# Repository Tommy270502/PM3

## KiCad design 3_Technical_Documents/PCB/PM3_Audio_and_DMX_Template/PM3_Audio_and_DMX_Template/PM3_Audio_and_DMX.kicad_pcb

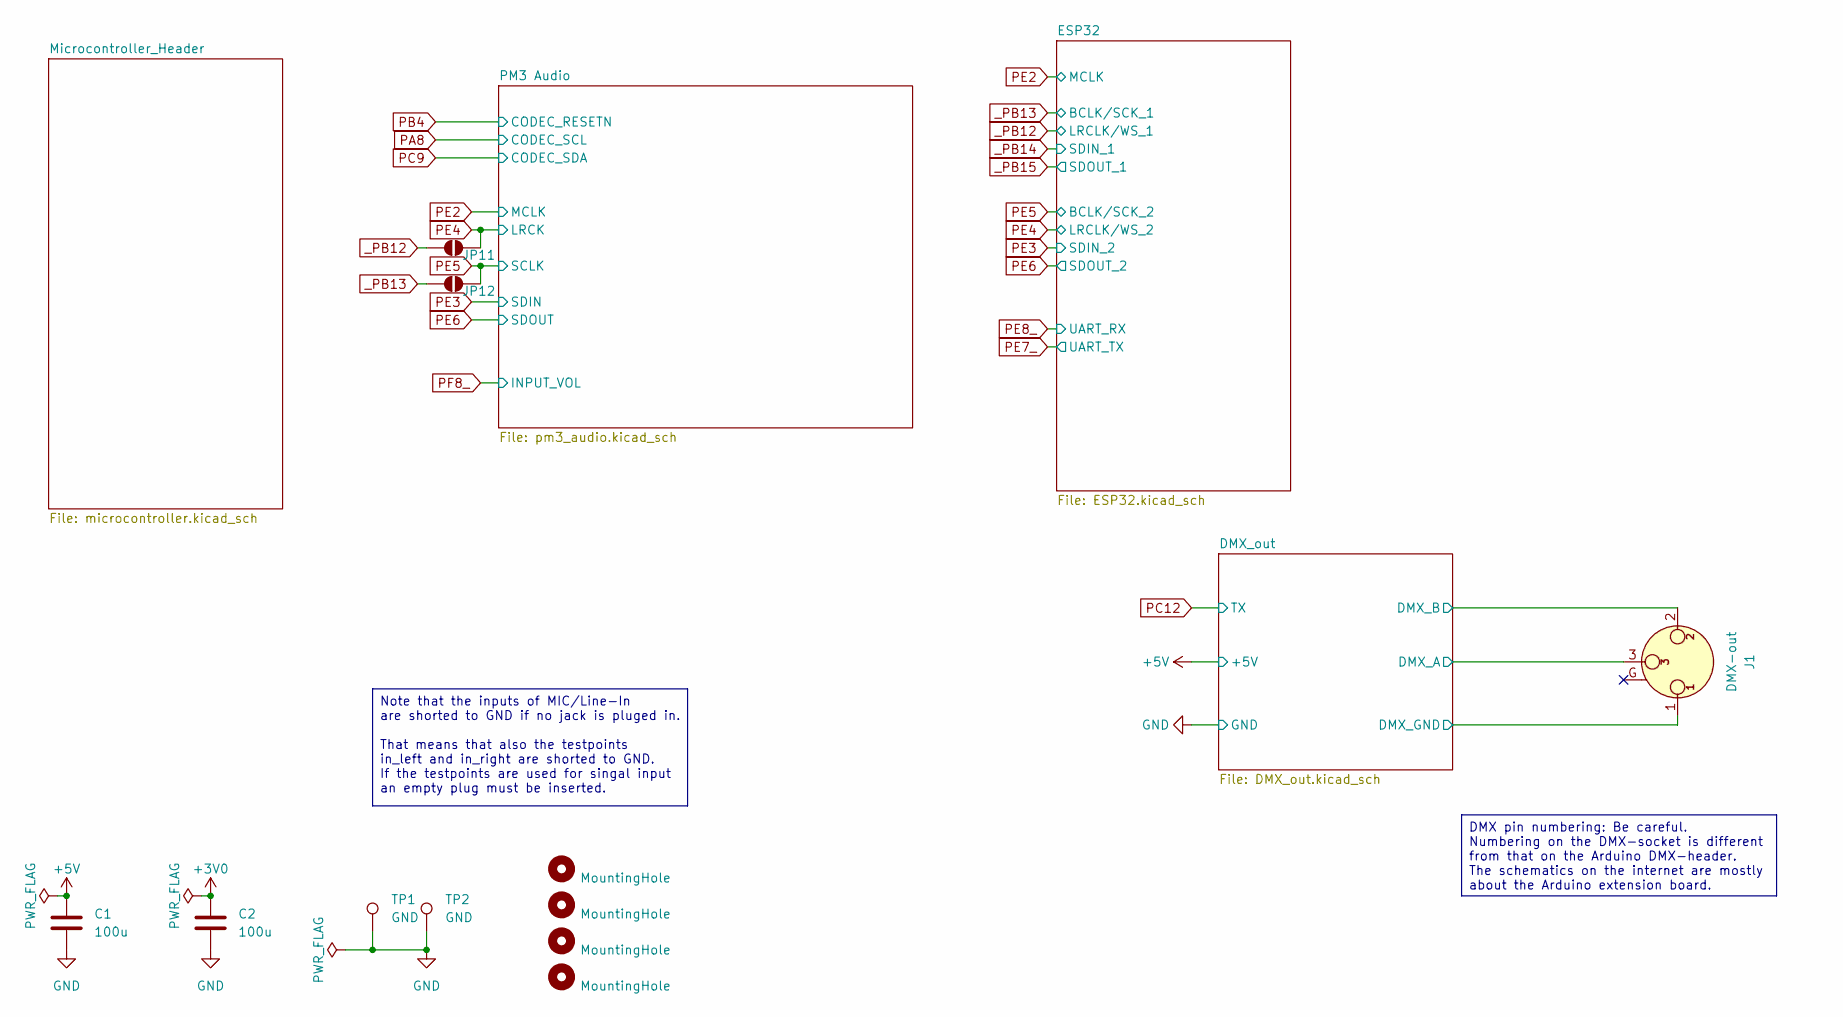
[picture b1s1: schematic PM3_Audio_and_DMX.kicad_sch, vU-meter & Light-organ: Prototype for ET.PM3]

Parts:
C1, C2: 100u; C_1206_3216Metric_Pad1.33x1.80mm_HandSolder; MPN C3216X5R1A107M160AC
H1, H2, H3, H4: MountingHole; MountingHole_3.2mm_M3_Pad_TopBottom
J1: DMX-out; Jack_XLR_Neutrik_NC3FAAH2_Horizontal
JP11, JP12: SolderJumper_2_Open; SolderJumper-2_P1.3mm_Open_RoundedPad1.0x1.5mm
TP1, TP2: GND; TestPoint_Loop_D2.60mm_Drill1.6mm_Beaded

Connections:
+5V: C1.1; also elsewhere on the board
/DMX_out/DMX_A: J1.3; also elsewhere on the board
/DMX_out/DMX_B: J1.2; also elsewhere on the board
DMX_GND: J1.1; also elsewhere on the board
GND: C1.2, C2.2, TP1.1, TP2.1; also elsewhere on the board
PE4: JP11.2 (B); also elsewhere on the board
PE5: JP12.2 (B); also elsewhere on the board
VL: C2.1; also elsewhere on the board
_PB12: JP11.1 (A); also elsewhere on the board
_PB13: JP12.1 (A); also elsewhere on the board

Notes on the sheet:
Note that the inputs of MIC/Line-In are shorted to GND if no jack is pluged in. That means that also the testpoints in_left and in_right are shorted to GND. If the testpoints are used for singal input an empty plug must be inserted.
DMX pin numbering: Be careful. Numbering on the DMX-socket is different from that on the Arduino DMX-header. The schematics on the internet are mostly about the Arduino extension board.

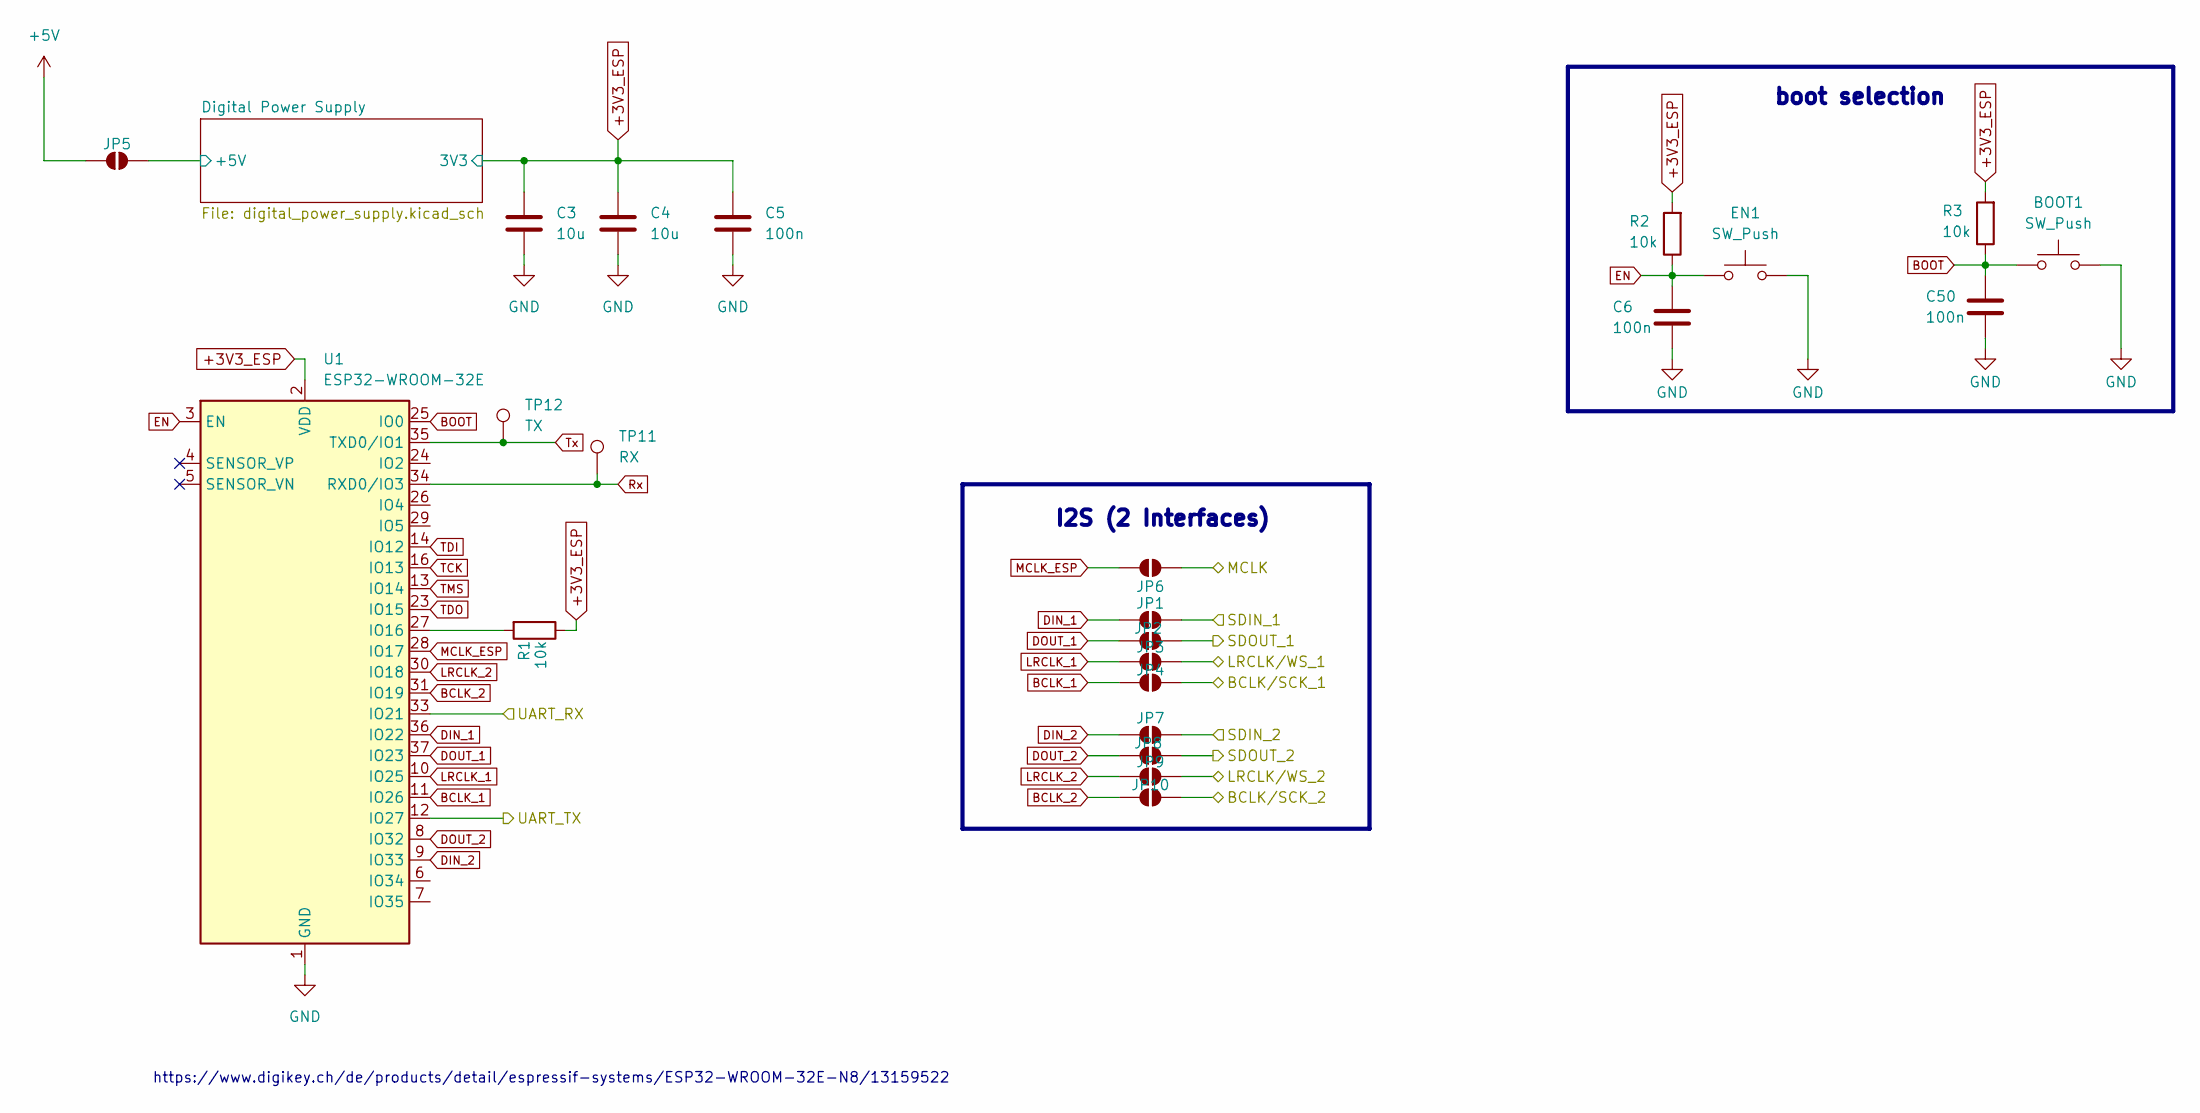
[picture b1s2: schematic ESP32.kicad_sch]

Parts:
BOOT1: SW_Push; SW_SPST_TL3342
C3, C4: 10u; C_1210_3225Metric; MPN GJ832ER7YA106KA12L
C5, C6, C50: 100n; C_0603_1608Metric; MPN GPC0603104-X7R
EN1: SW_Push; SW_SPST_TL3342
JP1, JP2, JP3, JP4, JP5, JP6, JP7, JP8, JP9, JP10: SolderJumper_2_Open; SolderJumper-2_P1.3mm_Open_RoundedPad1.0x1.5mm
R1, R2, R3: 10k; R_0603_1608Metric; MPN GPR060310K
TP11: RX
TP12: TX
U1: ESP32-WROOM-32E; ESP32-WROOM-32D

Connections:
+3V3_ESP: C3.1, C4.1, C5.1, R1.1, R2.2, R3.2, U1.2 (VDD); also elsewhere on the board
+5V: JP5.1 (A); also elsewhere on the board
/ESP32/Digital Power Supply/+5V: JP5.2 (B); also elsewhere on the board
BCLK_1: JP4.1 (A), U1.11 (IO26)
BCLK_2: JP10.1 (A), U1.31 (IO19)
BOOT: BOOT1.2, C50.1, R3.1, U1.25 (IO0)
DIN_1: JP1.1 (A), U1.36 (IO22)
DIN_2: JP7.1 (A), U1.9 (IO33)
DOUT_1: JP2.1 (A), U1.37 (IO23)
DOUT_2: JP8.1 (A), U1.8 (IO32)
EN: C6.1, EN1.2, R2.1, U1.3 (EN)
GND: BOOT1.1, C3.2, C4.2, C5.2, C6.2, C50.2, EN1.1, U1.1 (GND), U1.15 (GND), U1.38 (GND), U1.39 (GND); also elsewhere on the board
LRCLK_1: JP3.1 (A), U1.10 (IO25)
LRCLK_2: JP9.1 (A), U1.30 (IO18)
MCLK_ESP: JP6.1 (A), U1.28 (IO17)
unnamed: R1.2, U1.27 (IO16)
PE2: JP6.2 (B); also elsewhere on the board
PE3: JP7.2 (B); also elsewhere on the board
PE4: JP9.2 (B); also elsewhere on the board
PE5: JP10.2 (B); also elsewhere on the board
PE6: JP8.2 (B); also elsewhere on the board
PE7_: U1.12 (IO27); also elsewhere on the board
PE8_: U1.33 (IO21); also elsewhere on the board
Rx: TP11.1, U1.34 (RXD0/IO3)
TCK: U1.16 (IO13)
TDI: U1.14 (IO12)
TDO: U1.23 (IO15)
TMS: U1.13 (IO14)
Tx: TP12.1, U1.35 (TXD0/IO1)
_PB12: JP3.2 (B); also elsewhere on the board
_PB13: JP4.2 (B); also elsewhere on the board
_PB14: JP1.2 (B); also elsewhere on the board
_PB15: JP2.2 (B); also elsewhere on the board

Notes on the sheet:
boot selection
https://www.digikey.ch/de/products/detail/espressif-systems/ESP32-WROOM-32E-N8/13159522
I2S (2 Interfaces)

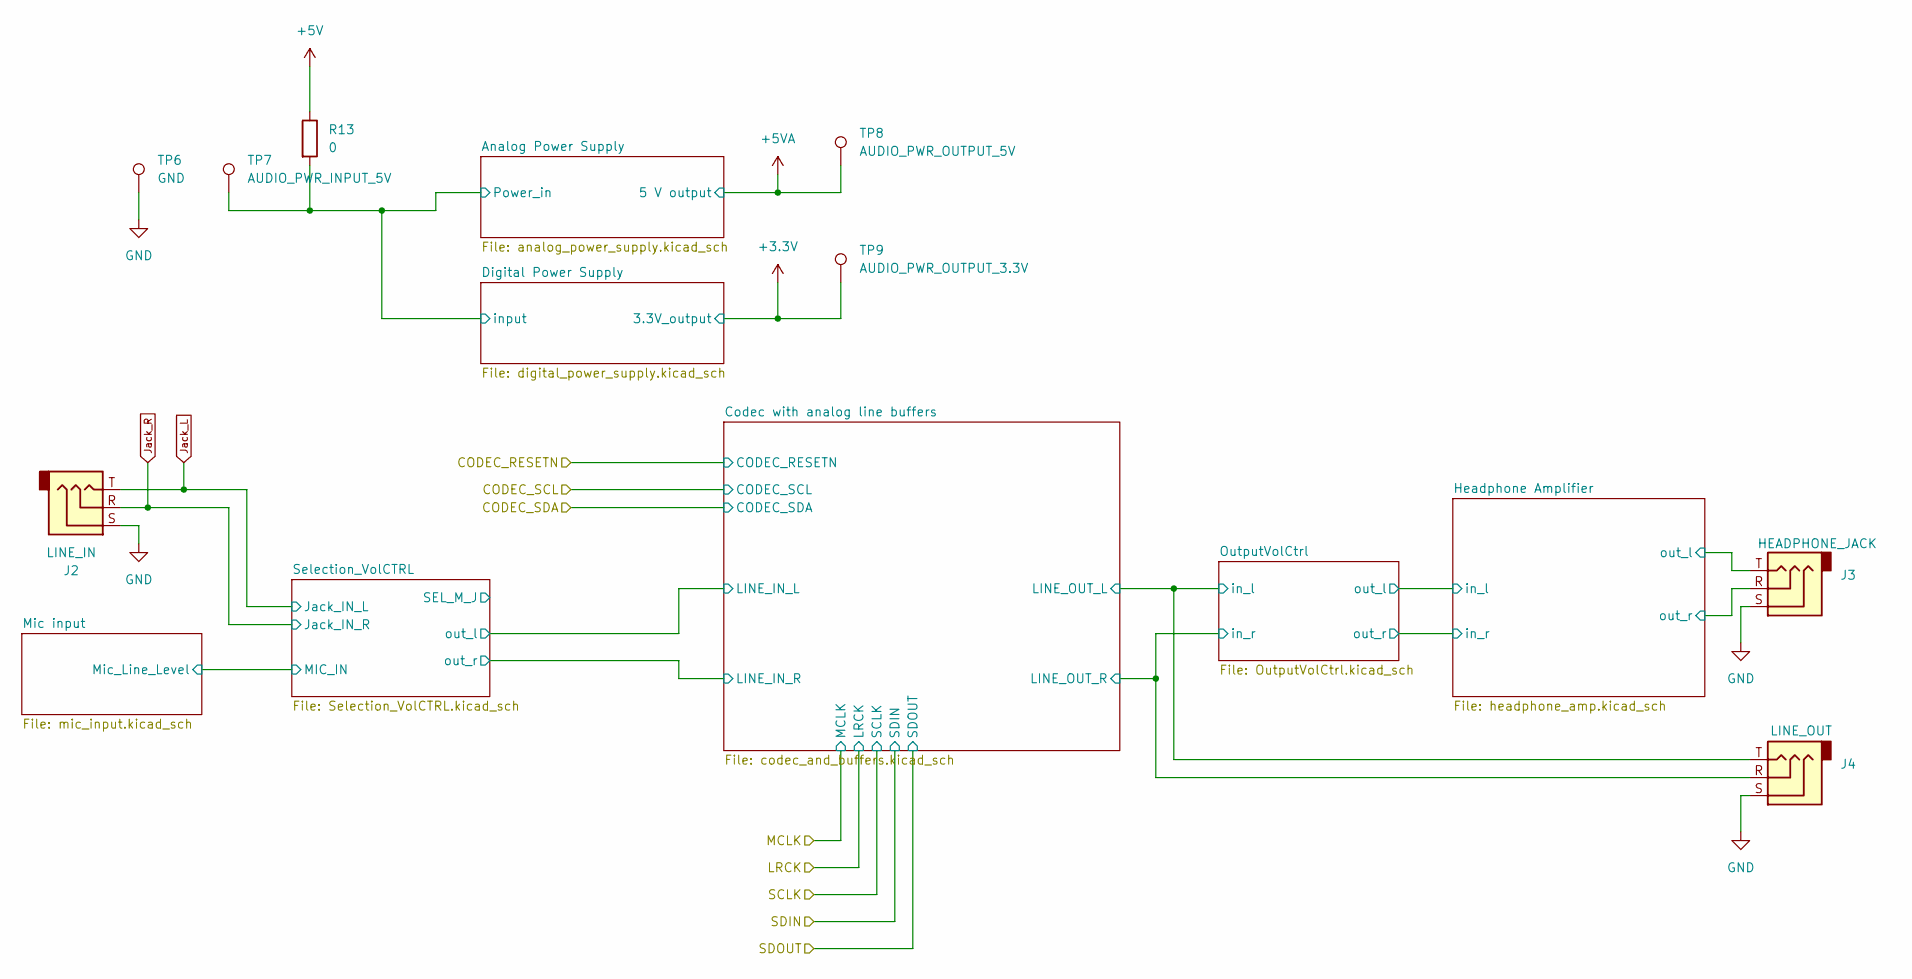
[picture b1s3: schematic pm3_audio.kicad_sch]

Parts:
J2: LINE_IN; Jack_3.5mm_CUI_SJ-3523-SMT_Horizontal; MPN SJ-3523-SMT-TR
J3: HEADPHONE_JACK; Jack_3.5mm_CUI_SJ-3523-SMT_Horizontal; MPN SJ-3523-SMT-TR
J4: LINE_OUT; Jack_3.5mm_CUI_SJ-3523-SMT_Horizontal; MPN SJ-3523-SMT-TR
R13: 0; R_0603_1608Metric; MPN GPR06030R
TP6: GND; TestPoint_Loop_D2.60mm_Drill1.6mm_Beaded
TP7: AUDIO_PWR_INPUT_5V; TestPoint_Loop_D2.60mm_Drill1.6mm_Beaded
TP8: AUDIO_PWR_OUTPUT_5V; TestPoint_Loop_D2.60mm_Drill1.6mm_Beaded
TP9: AUDIO_PWR_OUTPUT_3.3V; TestPoint_Loop_D2.60mm_Drill1.6mm_Beaded

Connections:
+5V: R13.1; also elsewhere on the board
/PM3 Audio/Analog Power Supply/Power_in: R13.2, TP7.1; also elsewhere on the board
/PM3 Audio/Codec with analog line buffers/LINE_OUT_L: J4.T; also elsewhere on the board
/PM3 Audio/Codec with analog line buffers/LINE_OUT_R: J4.R; also elsewhere on the board
/PM3 Audio/Headphone Amplifier/out_l: J3.T; also elsewhere on the board
/PM3 Audio/Headphone Amplifier/out_r: J3.R; also elsewhere on the board
GND: J2.S, J3.S, J4.S, TP6.1; also elsewhere on the board
Jack_L: J2.T; also elsewhere on the board
Jack_R: J2.R; also elsewhere on the board
VA: TP8.1; also elsewhere on the board
VD: TP9.1; also elsewhere on the board

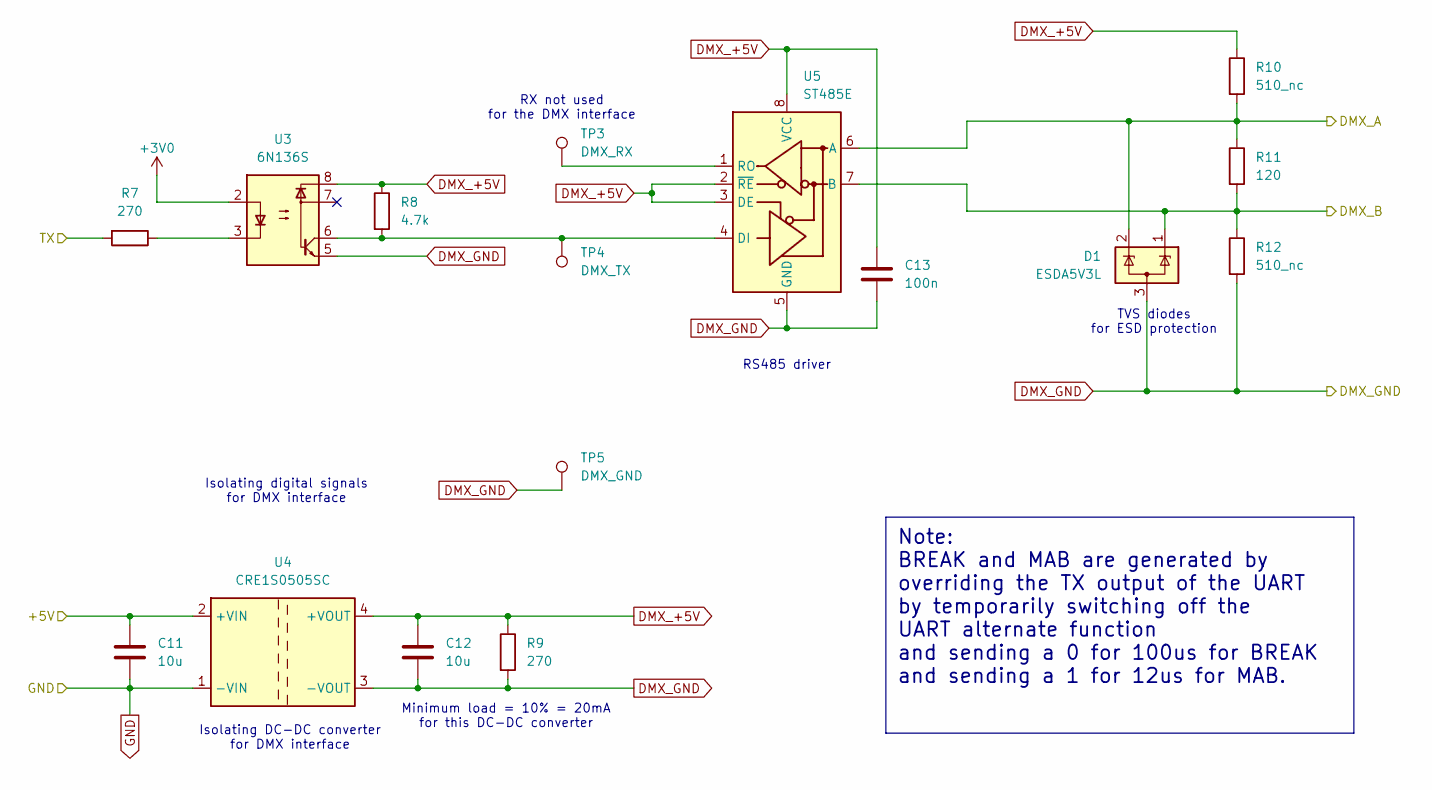
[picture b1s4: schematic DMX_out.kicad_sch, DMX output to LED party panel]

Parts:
C11, C12: 10u; C_0805_2012Metric_Pad1.18x1.45mm_HandSolder; MPN GPC0805106-35
C13: 100n; C_0805_2012Metric_Pad1.18x1.45mm_HandSolder; MPN GPC0805104
D1: ESDA5V3L; SOT-23-3; MPN ESDA5V3L
R7: 270; R_0603_1608Metric; MPN GPR0603270R
R8: 4.7k; R_0603_1608Metric; MPN GPR06034K7
R9: 270; R_0805_2012Metric; MPN GPR0805270R
R10, R12: 510_nc; R_0603_1608Metric
R11: 120; R_1206_3216Metric; MPN GPR1206120R
TP3: DMX_RX; TestPoint_Loop_D2.60mm_Drill1.6mm_Beaded
TP4: DMX_TX; TestPoint_Loop_D2.60mm_Drill1.6mm_Beaded
TP5: DMX_GND; TestPoint_Loop_D2.60mm_Drill1.6mm_Beaded
U3: 6N136S; SMDIP-8_W9.53mm; MPN 6N136S
U4: CRE1S0505SC; Converter_DCDC_Murata_CRE1xxxxxxSC_THT; MPN CRE1S0505SC
U5: ST485E; SOIC-8_3.9x4.9mm_P1.27mm; MPN ST485EBDR

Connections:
+5V: C11.1, U4.2 (+VIN); also elsewhere on the board
/DMX_out/DMX_A: D1.2 (K), R10.2, R11.1, U5.6 (A); also elsewhere on the board
/DMX_out/DMX_B: D1.1 (K), R11.2, R12.1, U5.7 (B); also elsewhere on the board
DMX_+5V: C12.1, C13.1, R8.1, R9.1, R10.1, U3.8, U4.4 (+VOUT), U5.2 (~RE), U5.3 (DE), U5.8 (VCC)
DMX_GND: C12.2, C13.2, D1.3 (A), R9.2, R12.2, TP5.1, U3.5, U4.3 (-VOUT), U5.5 (GND); also elsewhere on the board
GND: C11.2, U4.1 (-VIN); also elsewhere on the board
unnamed: R7.1, U3.3
unnamed: R8.2, TP4.1, U3.6, U5.4 (DI)
unnamed: TP3.1, U5.1 (RO)
PC12: R7.2; also elsewhere on the board
VL: U3.2; also elsewhere on the board

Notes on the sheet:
TVS diodes for ESD protection
Isolating digital signals for DMX interface
RX not used for the DMX interface
Minimum load = 10% = 20mA for this DC-DC converter
Isolating DC-DC converter for DMX interface
RS485 driver
Note: BREAK and MAB are generated by overriding the TX output of the UART by temporarily switching off the UART alternate function and sending a 0 for 100us for BREAK and sending a 1 for 12us for MAB.

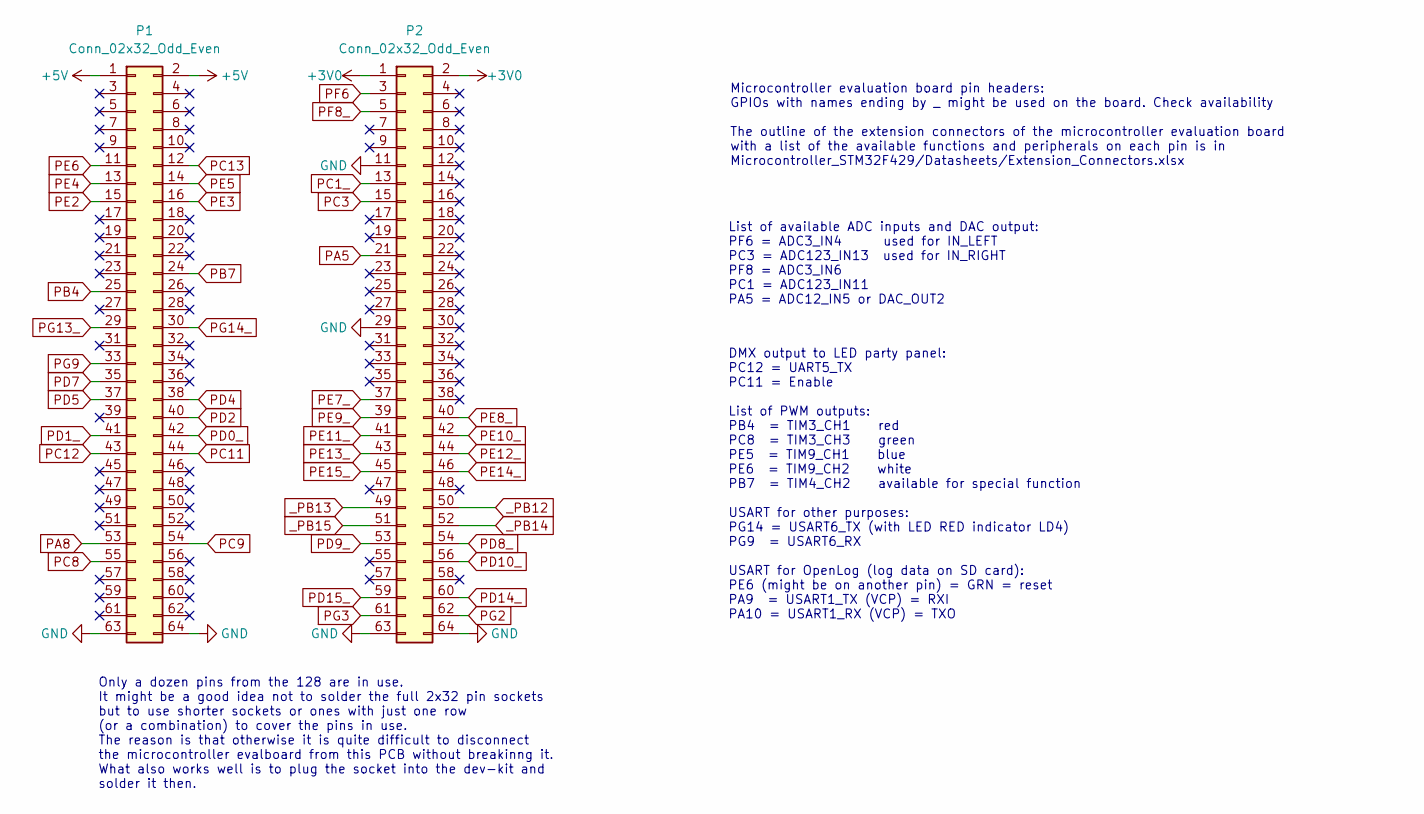
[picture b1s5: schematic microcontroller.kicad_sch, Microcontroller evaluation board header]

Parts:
P1, P2: Conn_02x32_Odd_Even; PinSocket_2x32_P2.54mm_Vertical

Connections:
+5V: P1.1, P1.2; also elsewhere on the board
GND: P1.63, P1.64, P2.11, P2.29, P2.63, P2.64; also elsewhere on the board
PA5: P2.21
PA8: P1.53; also elsewhere on the board
PB4: P1.25; also elsewhere on the board
PB7: P1.24
PC1_: P2.13
PC3: P2.15
PC8: P1.55
PC9: P1.54; also elsewhere on the board
PC11: P1.44
PC12: P1.43; also elsewhere on the board
PC13: P1.12
PD0_: P1.42
PD1_: P1.41
PD2: P1.40
PD4: P1.38
PD5: P1.37
PD7: P1.35
PD8_: P2.54
PD9_: P2.53
PD10_: P2.56
PD14_: P2.60
PD15_: P2.59
PE2: P1.15; also elsewhere on the board
PE3: P1.16; also elsewhere on the board
PE4: P1.13; also elsewhere on the board
PE5: P1.14; also elsewhere on the board
PE6: P1.11; also elsewhere on the board
PE7_: P2.37; also elsewhere on the board
PE8_: P2.40; also elsewhere on the board
PE9_: P2.39
PE10_: P2.42
PE11_: P2.41
PE12_: P2.44
PE13_: P2.43
PE14_: P2.46
PE15_: P2.45
PF6: P2.3
PF8_: P2.5
PG2: P2.62
PG3: P2.61
PG9: P1.33
PG13_: P1.29
PG14_: P1.30
VL: P2.1, P2.2; also elsewhere on the board
_PB12: P2.50; also elsewhere on the board
_PB13: P2.49; also elsewhere on the board
_PB14: P2.52; also elsewhere on the board
_PB15: P2.51; also elsewhere on the board

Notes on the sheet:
Only a dozen pins from the 128 are in use. It might be a good idea not to solder the full 2x32 pin sockets but to use shorter sockets or ones with just one row (or a combination) to cover the pins in use. The reason is that otherwise it is quite difficult to disconnect the microcontroller evalboard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
DMX output to LED party panel: PC12 = UART5_TX PC11 = Enable List of PWM outputs: PB4 = TIM3_CH1 red PC8 = TIM3_CH3 green PE5 = TIM9_CH1 blue PE6 = TIM9_CH2 white PB7 = TIM4_CH2 available for special function USART for other purposes: PG14 = USART6_TX (with LED RED indicator LD4) PG9 = USART6_RX US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
Microcontroller evaluation board pin headers: GPIOs with names ending by _ might be used on the board. Check availability The outline of the extension connectors of the microcontroller evaluation board with a list of the available functions and peripherals on each pin is in Microcontroller_STM32F42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
List of available ADC inputs and DAC output: PF6 = ADC3_IN4 used for IN_LEFT PC3 = ADC123_IN13 used for IN_RIGHT PF8 = ADC3_IN6 PC1 = ADC123_IN11 PA5 = ADC12_IN5 or DAC_OUT2

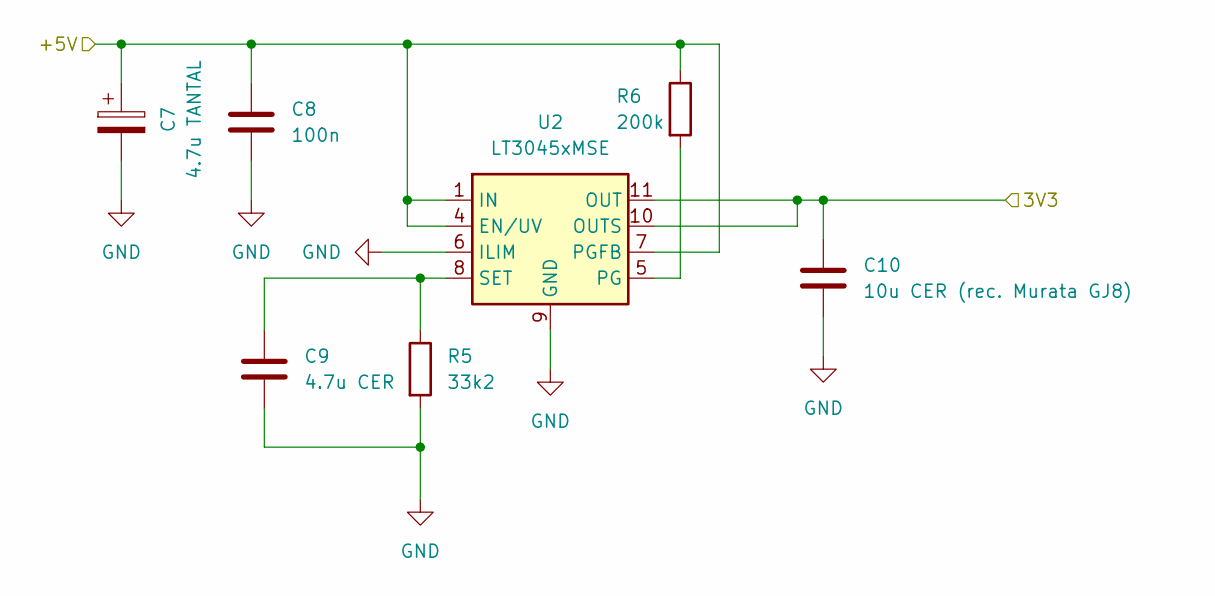
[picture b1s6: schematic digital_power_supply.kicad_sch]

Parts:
C7: 4.7u TANTAL; CP_EIA-3216-18_Kemet-A; MPN T495A475K010ATE1K3
C8: 100n; C_0603_1608Metric; MPN GPC0603104-X7R
C9: 4.7u CER; C_1210_3225Metric; MPN GPC1210475
C10: 10u CER (rec. Murata GJ8); C_1210_3225Metric; MPN GJ832ER7YA106KA12L
R5: 33k2; R_0603_1608Metric; MPN RC0603FR-0749K9L
R6: 200k; R_0603_1608Metric; MPN GPR0603200K
U2: LT3045xMSE; MSOP-12-1EP_3x4.039mm_P0.65mm_EP1.651x2.845mm; MPN LT3045EMSE

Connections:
+3V3_ESP: C10.1, U2.10 (OUTS), U2.11 (OUT), U2.12 (OUT); also elsewhere on the board
/ESP32/Digital Power Supply/+5V: C7.1, C8.1, R6.1, U2.1 (IN), U2.2 (IN), U2.3 (IN), U2.4 (EN/UV), U2.7 (PGFB); also elsewhere on the board
GND: C7.2, C8.2, C9.2, C10.2, R5.2, U2.6 (ILIM), U2.9 (GND), U2.13 (GND); also elsewhere on the board
unnamed: R6.2, U2.5 (PG)
unnamed: C9.1, R5.1, U2.8 (SET)

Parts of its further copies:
C26: 4.7u TANTAL; CP_EIA-3216-18_Kemet-A; MPN T495A475K010ATE1K3
C27: 100n; C_0603_1608Metric; MPN GPC0603104-X7R
C28: 4.7u CER; C_1210_3225Metric; MPN GPC1210475
C29: 10u CER (rec. Murata GJ8); C_1210_3225Metric; MPN GJ832ER7YA106KA12L
R26: 33k2; R_0603_1608Metric; MPN RC0603FR-0749K9L
R27: 200k; R_0603_1608Metric; MPN GPR0603200K
U9: LT3045xMSE; MSOP-12-1EP_3x4.039mm_P0.65mm_EP1.651x2.845mm; MPN LT3045EMSE

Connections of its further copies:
/PM3 Audio/Digital Power Supply/3V3: C29.1, U9.10 (OUTS), U9.11 (OUT), U9.12 (OUT)
/PM3 Audio/Digital Power Supply/+5V: C26.1, C27.1, R27.1, U9.1 (IN), U9.2 (IN), U9.3 (IN), U9.4 (EN/UV), U9.7 (PGFB)
GND: C26.2, C27.2, C28.2, C29.2, R26.2, U9.6 (ILIM), U9.9 (GND), U9.13 (GND); also elsewhere on the board
unnamed: R27.2, U9.5 (PG)
unnamed: C28.1, R26.1, U9.8 (SET)

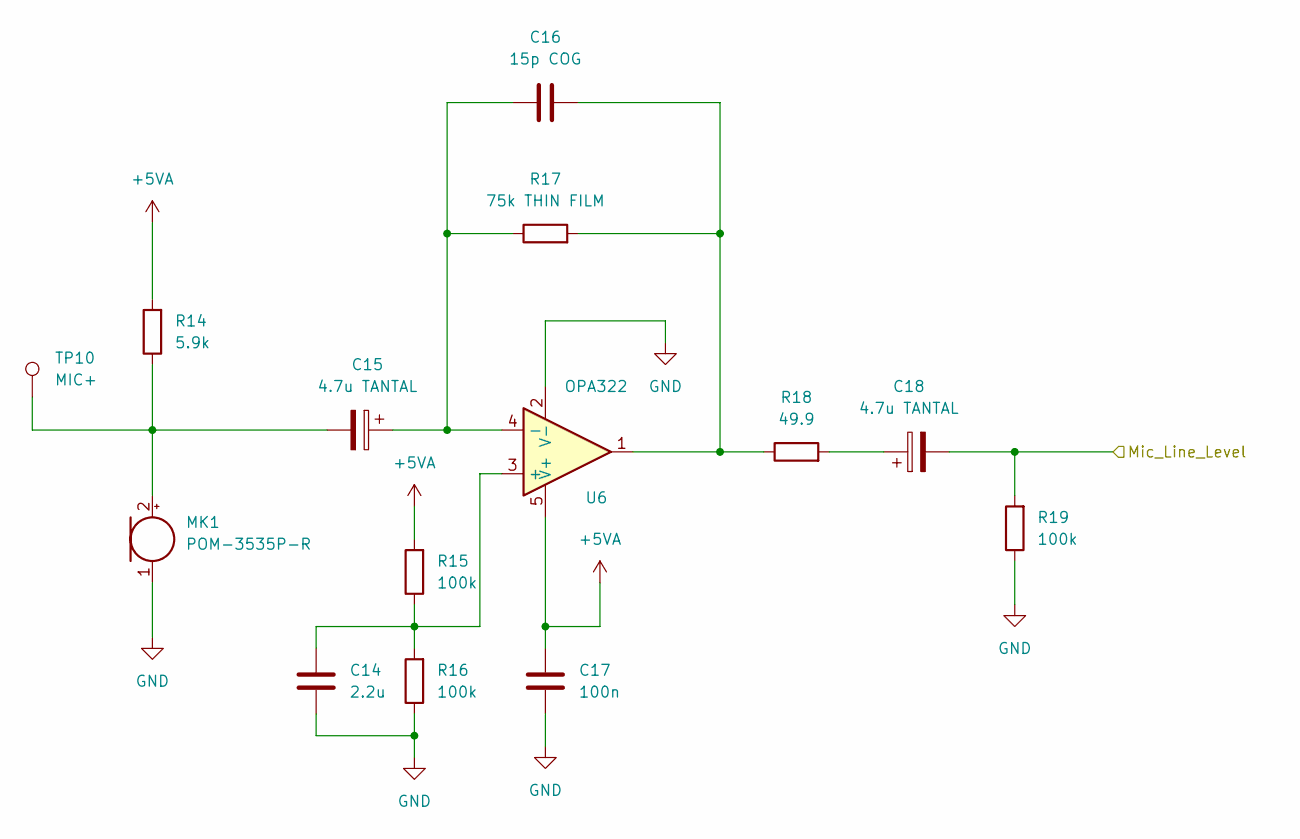
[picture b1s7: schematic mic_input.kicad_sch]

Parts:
C14: 2.2u; C_0805_2012Metric; MPN GPC0805225-25-X7R
C15, C18: 4.7u TANTAL; CP_EIA-3216-18_Kemet-A; MPN T495A475K010ATE1K3
C16: 15p COG; C_0603_1608Metric; MPN GPC0603150
C17: 100n; C_0603_1608Metric; MPN GPC0603104-X7R
MK1: POM-3535P-R; POM-2244P-C3310-2-R
R14: 5.9k; R_0603_1608Metric; MPN RT0603FRE075K9L
R15, R16, R19: 100k; R_0603_1608Metric; MPN GPR0603100K
R17: 75k THIN FILM; R_0603_1608Metric; MPN GPR060375K
R18: 49.9; R_0603_1608Metric; MPN 302-49.9-RC
TP10: MIC+; TestPoint_Loop_D2.60mm_Drill1.6mm_Beaded
U6: OPA322; SOT-23-5; MPN OPA322AIDBVT

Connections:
/PM3 Audio/Mic input/Mic_Line_Level: C18.2, R19.2; also elsewhere on the board
GND: C14.1, C17.1, MK1.1 (-), R16.1, R19.1, U6.2 (V-); also elsewhere on the board
unnamed: C16.2, R17.2, R18.1, U6.1
unnamed: C18.1, R18.2
unnamed: C15.2, MK1.2 (+), R14.1, TP10.1
unnamed: C14.2, R15.1, R16.2, U6.3 (+)
unnamed: C15.1, C16.1, R17.1, U6.4 (-)
VA: C17.2, R14.2, R15.2, U6.5 (V+); also elsewhere on the board

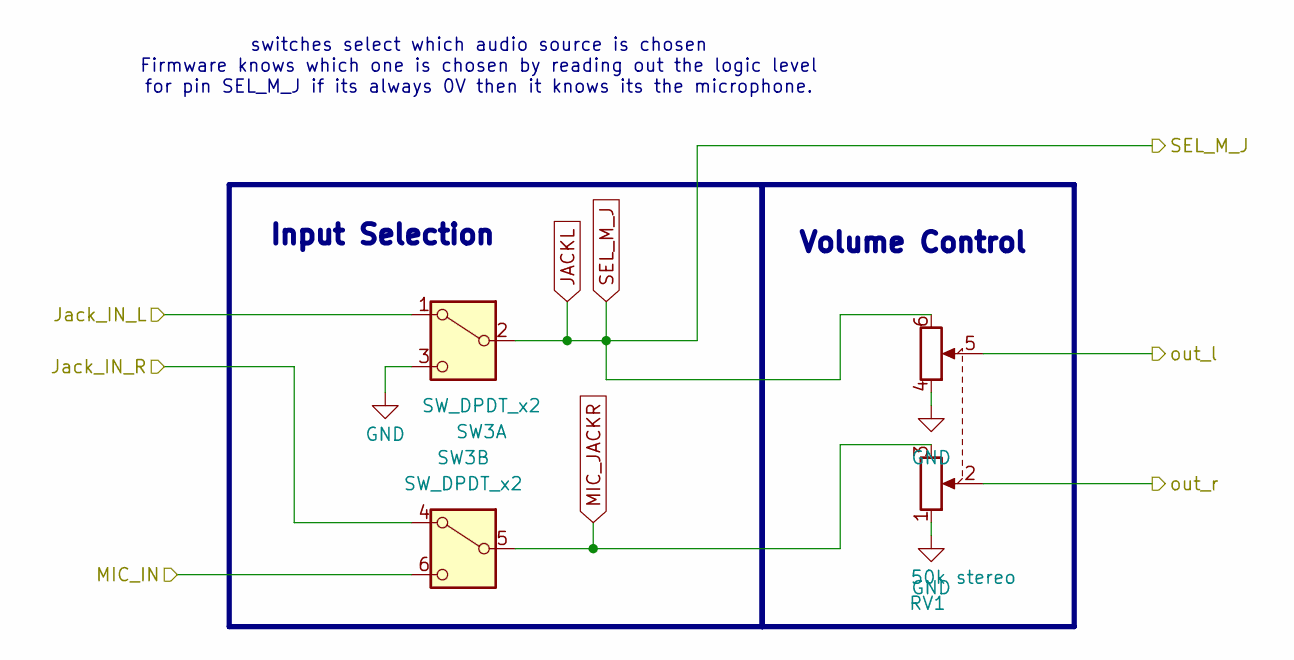
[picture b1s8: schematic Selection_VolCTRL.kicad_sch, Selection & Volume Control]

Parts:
RV1: 50k stereo; Potentiometer_Bourns_PTV112-4_Dual_Vertical
SW3: SW_DPDT_x2; SW_DPDT_CK_JS202011JCQN; MPN JS202011JCQN

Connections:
/PM3 Audio/Codec with analog line buffers/LINE_IN_L: RV1.5; also elsewhere on the board
/PM3 Audio/Codec with analog line buffers/LINE_IN_R: RV1.2; also elsewhere on the board
/PM3 Audio/Mic input/Mic_Line_Level: SW3.6 (C); also elsewhere on the board
GND: RV1.1, RV1.4, SW3.3 (C); also elsewhere on the board
JACKL: RV1.6, SW3.2 (B)
Jack_L: SW3.1 (A); also elsewhere on the board
Jack_R: SW3.4 (A); also elsewhere on the board
MIC_JACKR: RV1.3, SW3.5 (B)

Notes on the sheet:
switches select which audio source is chosen Firmware knows which one is chosen by reading out the logic level for pin SEL_M_J if its always 0V then it knows its the microphone.
Input Selection
Volume Control

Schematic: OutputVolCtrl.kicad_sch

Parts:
RV2: 50k stereo; Potentiometer_Bourns_PTV112-4_Dual_Vertical

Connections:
/PM3 Audio/Codec with analog line buffers/LINE_OUT_L: RV2.6; also elsewhere on the board
/PM3 Audio/Codec with analog line buffers/LINE_OUT_R: RV2.3; also elsewhere on the board
/PM3 Audio/Headphone Amplifier/in_l: RV2.5; also elsewhere on the board
/PM3 Audio/Headphone Amplifier/in_r: RV2.2; also elsewhere on the board
GND: RV2.1, RV2.4; also elsewhere on the board

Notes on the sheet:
Volume Control

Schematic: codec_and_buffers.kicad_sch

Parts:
C30, C31: 40p; C_0603_1608Metric; MPN GPC0603104-X7R
C32, C34, C36, C37, C38: 100n; C_0603_1608Metric; MPN GPC0603104-X7R
C33, C35, C39, C40: 1u; C_0805_2012Metric; MPN GPC0805105
C41: 47u; CP_Elec_6.3x7.7; MPN 865080645012
R4, R28, R29, R30, R31, R64: 10k; R_0603_1608Metric; MPN GPR060310K
R32: 47k; R_0603_1608Metric; MPN GPR060310K
R33, R34, R35, R36: 22R; R_0603_1608Metric; MPN GPR060310K
U10: CS4271; TSSOP-28_4.4x9.7mm_P0.65mm; MPN CS4271-CZZ
Y1: Crystal_SMD_5032-2Pin_5.0x3.2mm; MPN 445A22E24M57600

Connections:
/PM3 Audio/Codec with analog line buffers/Audio Input/AINA: U10.17 (AINA); also elsewhere on the board
/PM3 Audio/Codec with analog line buffers/Audio Input/AINB: U10.18 (AINB); also elsewhere on the board
/PM3 Audio/Codec with analog line buffers/Audio Output/AOUTA+: U10.25 (AOUTA+); also elsewhere on the board
/PM3 Audio/Codec with analog line buffers/Audio Output/AOUTA-: U10.24 (AOUTA-); also elsewhere on the board
/PM3 Audio/Codec with analog line buffers/Audio Output/AOUTB+: U10.26 (AOUTB+); also elsewhere on the board
/PM3 Audio/Codec with analog line buffers/Audio Output/AOUTB-: U10.27 (AOUTB-); also elsewhere on the board
GND: C30.1, C31.1, C32.2, C33.2, C34.2, C35.2, C36.2, C37.2, C38.1, C39.2, C40.2, C41.2, R29.1, R31.1, U10.8 (DGND), U10.21 (AGND); also elsewhere on the board
unnamed: R4.2, U10.13 (AD0/~CS(I2S/~LJ))
unnamed: C38.2, C41.1, U10.22 (FILT+)
unnamed: R34.1, U10.4 (LRCK)
unnamed: R33.2, U10.3 (MCLK)
unnamed: R35.1, U10.5 (SCLK)
unnamed: R36.1, U10.7 (SDIN)
PA8: R28.1, R29.2, U10.11 (SCL/CCLK(M0)); also elsewhere on the board
PB4: R64.1, U10.14 (~RST); also elsewhere on the board
PC9: R30.1, R31.2, U10.12 (SDA/CDIN(M1)); also elsewhere on the board
PE2: R33.1; also elsewhere on the board
PE3: R36.2; also elsewhere on the board
PE4: R34.2; also elsewhere on the board
PE5: R35.2; also elsewhere on the board
PE6: R32.1, U10.6 (SDOUT(M/~S)); also elsewhere on the board
VA: C36.1, C39.1, U10.20 (VA); also elsewhere on the board
VCOM: C37.1, C40.1, U10.15 (VQ1), U10.16 (VQ2), U10.19 (VQ3); also elsewhere on the board
VD: C34.1, C35.1, U10.9 (VD); also elsewhere on the board
VL: C32.1, C33.1, R4.1, R28.2, R30.2, R32.2, R64.2, U10.10 (VL); also elsewhere on the board
XTI: C30.2, U10.2 (XTI), Y1.2
XTO: C31.2, U10.1 (XT0), Y1.1

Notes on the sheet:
R30 dnp
R29 dnp

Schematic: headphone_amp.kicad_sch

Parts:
C66, C67: 4.7u TANTAL; CP_EIA-3216-18_Kemet-A; MPN T495A475K010ATE1K3
C68, C69: 5p COG; C_0603_1608Metric; MPN 06035A5R0CAT2A
C70: 1u; C_0805_2012Metric; MPN GPC0805105
C71: 100n LOW ESR; C_0603_1608Metric; MPN GPC0603104-X7R
C72, C73: 100u; CP_Elec_6.3x7.7; MPN 865060445005
C74: 10u; CP_Elec_6.3x7.7; MPN EEE-1HA100AP
R59, R60: 20k THIN FILM; R_0603_1608Metric; MPN GPR060320K
R61, R62: 100k THIN FILM; R_0603_1608Metric; MPN GPR0603100K
R63: 100k; R_0603_1608Metric; MPN GPR0603100K
U14: TPA6110A2DGN; HVSSOP-8-1EP_3x3mm_P0.65mm_EP1.57x1.89mm; MPN TPA6110A2DGN

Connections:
/PM3 Audio/Headphone Amplifier/in_l: C66.2; also elsewhere on the board
/PM3 Audio/Headphone Amplifier/in_r: C67.2; also elsewhere on the board
/PM3 Audio/Headphone Amplifier/out_l: C72.2; also elsewhere on the board
/PM3 Audio/Headphone Amplifier/out_r: C73.2; also elsewhere on the board
GND: C70.2, C71.2, C74.2, R63.1, U14.2 (GND), U14.9 (GND); also elsewhere on the board
unnamed: C66.1, R59.1
unnamed: C67.1, R60.1
unnamed: C70.1, U14.1 (BYPASS)
unnamed: C68.2, R59.2, R61.1, U14.8 (IN1-)
unnamed: C69.1, R60.2, R62.2, U14.4 (IN2-)
unnamed: R63.2, U14.3 (SHDN)
unnamed: C68.1, C72.1, R61.2, U14.7 (VO1)
unnamed: C69.2, C73.1, R62.1, U14.5 (VO2)
VA: C71.1, C74.1, U14.6 (VDD); also elsewhere on the board

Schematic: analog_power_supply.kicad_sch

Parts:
C19: 1u; CP_Elec_4x5.8; MPN EEE1HA010SR
C20, C22: 10u; C_1210_3225Metric; MPN GPC1210106
C21: 470p; C_0603_1608Metric; MPN GPC0603471
C23: 4.7u CER; C_1210_3225Metric; MPN GPC1210475
C24: 4.7u TANTAL; CP_EIA-3216-18_Kemet-A; MPN T495A475K010ATE1K3
C25: 10u CER (rec. Murata GJ8); C_1210_3225Metric; MPN GJ832ER7YA106KA12L
L1: 74438357022; L_Wuerth_MAPI-4030; MPN 74438357022
R20: 301k; R_0603_1608Metric
R21: 30k; R_0603_1608Metric; MPN GPR060330K
R22: 49.9k; R_0603_1608Metric; MPN RC0603FR-0749K9L
R23: 200k; R_0603_1608Metric; MPN GPR0603200K
R24: 700k; R_0603_1608Metric; MPN RMC1/16K6983DTP
R25: 50k; R_0603_1608Metric; MPN RC0603FR-0749K9L
U7: TLV61070ADBV; SOT-23-6; MPN TLV61070ADBVR
U8: LT3045xMSE; MSOP-12-1EP_3x4.039mm_P0.65mm_EP1.651x2.845mm; MPN LT3045EMSE

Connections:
/PM3 Audio/Analog Power Supply/Power_in: C19.1, C20.1, L1.1, U7.3 (EN), U7.6 (V_{IN}); also elsewhere on the board
GND: C19.2, C20.2, C22.2, C23.2, C24.2, C25.2, R21.2, R22.2, R25.2, U7.2 (GND), U8.6 (ILIM), U8.9 (GND), U8.13 (GND); also elsewhere on the board
unnamed: L1.2, U7.1 (SW)
unnamed: C21.2, R20.2, R21.1, U7.4 (V_{FB})
unnamed: C21.1, C22.1, C24.1, R20.1, R23.1, U7.5 (V_{OUT}), U8.1 (IN), U8.2 (IN), U8.3 (IN), U8.4 (EN/UV)
unnamed: R23.2, U8.5 (PG)
unnamed: R24.2, R25.1, U8.7 (PGFB)
unnamed: C23.1, R22.1, U8.8 (SET)
VA: C25.1, R24.1, U8.10 (OUTS), U8.11 (OUT), U8.12 (OUT); also elsewhere on the board

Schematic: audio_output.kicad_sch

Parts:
C52, C53: 2n2 COG; C_0603_1608Metric; MPN GPC0603222-C0G
C54, C55: 6n8 COG; C_0603_1608Metric; MPN GPC0603222-C0G
C56, C57, C64, C65: 22u; CP_Elec_6.3x7.7; MPN 865060543003
C58, C59: 1n5 COG; C_0603_1608Metric; MPN GPC0603222-C0G
C60: 100n; C_0603_1608Metric; MPN GPC0603104-X7R
C61, C62: 470p; C_0603_1608Metric; MPN GPC0603222-C0G
R43, R45: 4.53k; R_0603_1608Metric
R44, R46: 1k33; R_0603_1608Metric; MPN CPF0603F4K99C1
R47, R48: 1k5; R_0603_1608Metric; MPN CPF0603F4K99C1
R49, R51: 5.11k; R_0603_1608Metric
R50, R52: 715R; R_0603_1608Metric; MPN CPF0603F4K99C1
R53, R54: 2.26k; R_0603_1608Metric
R55, R56: 560R; R_0603_1608Metric; MPN CPF0603F4K99C1
R57, R58: 47k; R_0603_1608Metric; MPN CPF0603F4K99C1
U13: OPA2134; SOIC-8_3.9x4.9mm_P1.27mm; MPN OPA2134UA

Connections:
/PM3 Audio/Codec with analog line buffers/Audio Output/AOUTA+: R44.1; also elsewhere on the board
/PM3 Audio/Codec with analog line buffers/Audio Output/AOUTA-: R43.1; also elsewhere on the board
/PM3 Audio/Codec with analog line buffers/Audio Output/AOUTB+: R46.1; also elsewhere on the board
/PM3 Audio/Codec with analog line buffers/Audio Output/AOUTB-: R45.1; also elsewhere on the board
/PM3 Audio/Codec with analog line buffers/LINE_OUT_L: R55.2, R57.2; also elsewhere on the board
/PM3 Audio/Codec with analog line buffers/LINE_OUT_R: R56.2, R58.2; also elsewhere on the board
GND: C52.1, C53.1, C54.1, C55.1, C56.2, C57.2, C58.1, C59.1, C60.2, R57.1, R58.1, U13.4 (V-); also elsewhere on the board
unnamed: C52.2, R43.2, R49.1, R53.1
unnamed: C53.2, R45.2, R51.1, R54.1
unnamed: C54.2, R44.2, R47.1, R50.1
unnamed: C55.2, R46.2, R48.1, R52.1
unnamed: C56.1, R47.2
unnamed: C57.1, R48.2
unnamed: C61.2, C64.1, R53.2, U13.1
unnamed: C62.2, C65.1, R54.2, U13.7
unnamed: C64.2, R55.1
unnamed: C65.2, R56.1
unnamed: C58.2, R50.2, U13.3 (+)
unnamed: C61.1, R49.2, U13.2 (-)
unnamed: C59.2, R52.2, U13.5 (+)
unnamed: C62.1, R51.2, U13.6 (-)
VA: C60.1, U13.8 (V+); also elsewhere on the board

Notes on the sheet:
Analog Output
